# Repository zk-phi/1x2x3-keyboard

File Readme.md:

# Hifumi Keyboard

初心者向け自作キーボードキットです。

A tiny DIY keyboard for newbs.

実際にキーボードの組み立てを体験しながら自作キーボードに入門してもらえるよう、 [同人誌](https://riconken.bitbucket.io/hifumi/) の内容に合わせて設計しました。

## ファームウェア

ビルド済みのファームウェアのダウンロード (右クリックから保存してください)：

- [test キーマップ](https://raw.githubusercontent.com/zk-phi/1x2x3-keyboard/master/firmware/hifumi_test.hex)
  - 動作確認のためのキーマップです

- [default キーマップ](https://raw.githubusercontent.com/zk-phi/1x2x3-keyboard/master/firmware/hifumi_default.hex)
  - スクリーンショット (PrScr) など実用的なキーが配置されたキーマップです

ソースコードからビルドしたい場合は [QMK Firmware の公式リポジトリ](https://github.com/qmk/qmk_firmware) を参照してください。

## 組み立て

わかる人向けの近道ガイド。丁寧な解説は同人誌の方をどうぞ。

1. コンスルー (H=2.5mm) を ProMicro に実装

   https://github.com/zk-phi/keyboard-buildguide-common/blob/master/conthrough.markdown

2. SK6812mini Neopixel LED を実装 (optional)

   https://github.com/zk-phi/keyboard-buildguide-common/blob/master/neopixel.markdown

3. 1N4818 (または 1N4148w) ダイオードを実装

   https://github.com/zk-phi/keyboard-buildguide-common/blob/master/diode.markdown

4. MX 互換スイッチをトッププレートにはめ、基板と合体して半田付け

   https://github.com/zk-phi/keyboard-buildguide-common/blob/master/switch.markdown

5. M2 ネジ・高ナットでボトムプレートを連結

## 基板の発注

自分で基板を発注してみたい人向け。

1. [KiCAD](https://kicad.org/) をインストールして、プロジェクト `pcb/surfboard.pro` を開く

2. 基板データ `surfboard.kicad_pcb` をダブルクリックして基板エディタ (Pcbnew) を立ち上げる

3. `ファイル (F) > プロット (l)` で製造ファイルの出力画面を開き、設定する

   必要なレイヤーにチェックを入れる他は、基本的にデフォルトのままで問題ないと思います

   - 出力フォーマット：ガーバー

   - 含まれるレイヤー：
     - F.Cu (配線 - 表)
     - B.Cu (配線 - 裏)
     - F.SilkS (シルク印刷 - 表)
     - B.SilkS (シルク印刷 - 裏)
     - F.Mask (レジスト塗装 - 表)
     - B.Mask (レジスト塗装 - 裏)
     - Edge.Cuts (基板外形)

   - 一般オプション：
     - フットプリントの定数をプロット
     - フットプリントのリファレンスをプロット
     - 基板外形レイヤーのデータを他のレイヤーから除外 (外形専用のレイヤーに出力するので不要)
     - シルクからパッドを除外 (シルク印刷がパッドに被っているところをいい感じにしてくれる)
     - プロット前にゾーンの塗り潰しをチェック (データが変になってると警告してくれる)

   `フットプリントの xx をプロット` 系のオプションは hifumi の場合どっちでもいいです (使っていないので)。

4. `製造ファイルを出力` でガーバーデータを生成

5. `ドリルファイルを生成` でドリルファイルの出力画面を開き、設定する

   以下のデフォルト設定で特に困ったことがないです

   - ファイル形式: Excellon
   - 単位:  mm
   - ゼロのフォーマット: 小数点フォーマット
   - マップファイルフォーマット: (マップファイルは使用しません)
   - ドリルファイルオプション: 特になし
   - ドリル原点: 絶対位置

6. `ドリルファイルを生成` でドリルファイルを生成

7. 各製造業者の指定するファイル名に直す

   便利スクリプトあります: `pcb/rename-elecrow.sh`

   elecrow の場合、

   - ガーバー
     - `<プロジェクト名>-F.Cu.gbr` => `<プロジェクト名>.GTL`
     - `<プロジェクト名>-B.Cu.gbr` => `<プロジェクト名>.GBL`
     - `<プロジェクト名>-F.Mask.gbr` => `<プロジェクト名>.GTS`
     - `<プロジェクト名>-B.Mask.gbr` => `<プロジェクト名>.GBS`
     - `<プロジェクト名>-F.SilkS.gbr` => `<プロジェクト名>.GTO`
     - `<プロジェクト名>-B.SilkS.gbr` => `<プロジェクト名>.GBO`
     - `<プロジェクト名>-Edge.Cuts.gbr` => `<プロジェクト名>.GML`

   - ドリル
     - `<プロジェクト名>-PTH.drl` => `<プロジェクト名>.TXT`
     - `<プロジェクト名>-NPTH.drl` => `<プロジェクト名>-NPTH.TXT`

   と改名して、 zip に固めれば ok

   ファイルが足りない場合は手順を確認してやり直してください

8. 基板製造業者のオーダーページを開いて、ガーバーをアップロード

   サイトによっては基板サイズなどをこの時点で自動計算してくれる場合があります

9. フォームを埋めてオーダーする

   どのサイトでも確認した方がいいのは主に以下：

   - レイヤー数 layers: 2 (表と裏)
   - サイズ dimensions: 65 x 46 mm (小数点以下は切り上げで ok)
   - 作る枚数 qty
   - デザイン数 different design: 1
   - 厚み thickness: 1.6 mm
   - レジストの色 PCB (mask) color: お好みで
   - シルク印刷の色 silkscreen color: お好みで
   - パッドの表面仕上げ surface finish: HASL (Lead-free にすると鉛フリー, Gold にすると金ピカ)

   JLCPCB などの場合、追加料金を払わないと管理番号を印刷されてしまう場合があります:

   - 製造番号を消す remove order no: お好みで

   その他、サイトによって細かい技術仕様を申告する欄がありますが (すごい小さい穴を開けたい場合追加料金とか)、 hifumi の場合はそのままで大丈夫だと思います。

## プレートのレーザーカット

自分でプレートを切ってみたい人向け。

1. [OpenSCAD](https://www.openscad.org/) をインストールして、 `case/surfbord.scad` を開く

2. プログラム末尾の以下の行を書き換えて、必要な大きさのモデルを表示

   ```scad
   //cut_model_100x100();
   //cut_model_150x100();
   //cut_model_300x300();
   preview();
   ```

   デフォルトではキーボード全体のプレビューが表示されています。

   `prevew()` の行をコメントアウトして、たとえば `cut_model_100x100()` の行のコメントアウトを解除すると、 100mm x 100mm の板から切り出すためのモデルが表示されます。

   ```diff
   -//cut_model_100x100();
   +cut_model_100x100();
    //cut_model_150x100();
    //cut_model_300x300();
   -preview();
   +//preview();
   ```

   発注先のサイトや、レンタルするマシンの仕様に応じて適切なものを選んでください

   100x100 １枚からは１台分、 150x100 １枚からは２台分、 300x300 １枚からは１２台分が取れます。

3. `Design > Render (F6)` でレンダリングを実行

   一瞬で終わります

4. `File > Export > Export as DXF` で DXF ファイルを作成

   レーザーカッターでよく使われるファイル形式です

5. レーザーカットサービスに依頼したり、工房でレーザーカッターをレンタルして切る

   板は 3mm 厚のものを選んでください

   elecrow で `cut_model_100x100()` を切ってもらう場合の例:

   - Size: `10cm x 10cm Max (Thickness 3.0mm)`
   - Color: お好みで
   - Lead Time: 3-5 日固定 (執筆時点)
   - File: (`.dxf` を `.zip` に圧縮してアップロード)

   まれに変な寸法で作られてしまうことがあるので、もし連絡欄などがあれば

   - FYI: 四角い穴は 14mm x 14mm が正しいです

   などと補足をいれておいてもいいかもしれないです

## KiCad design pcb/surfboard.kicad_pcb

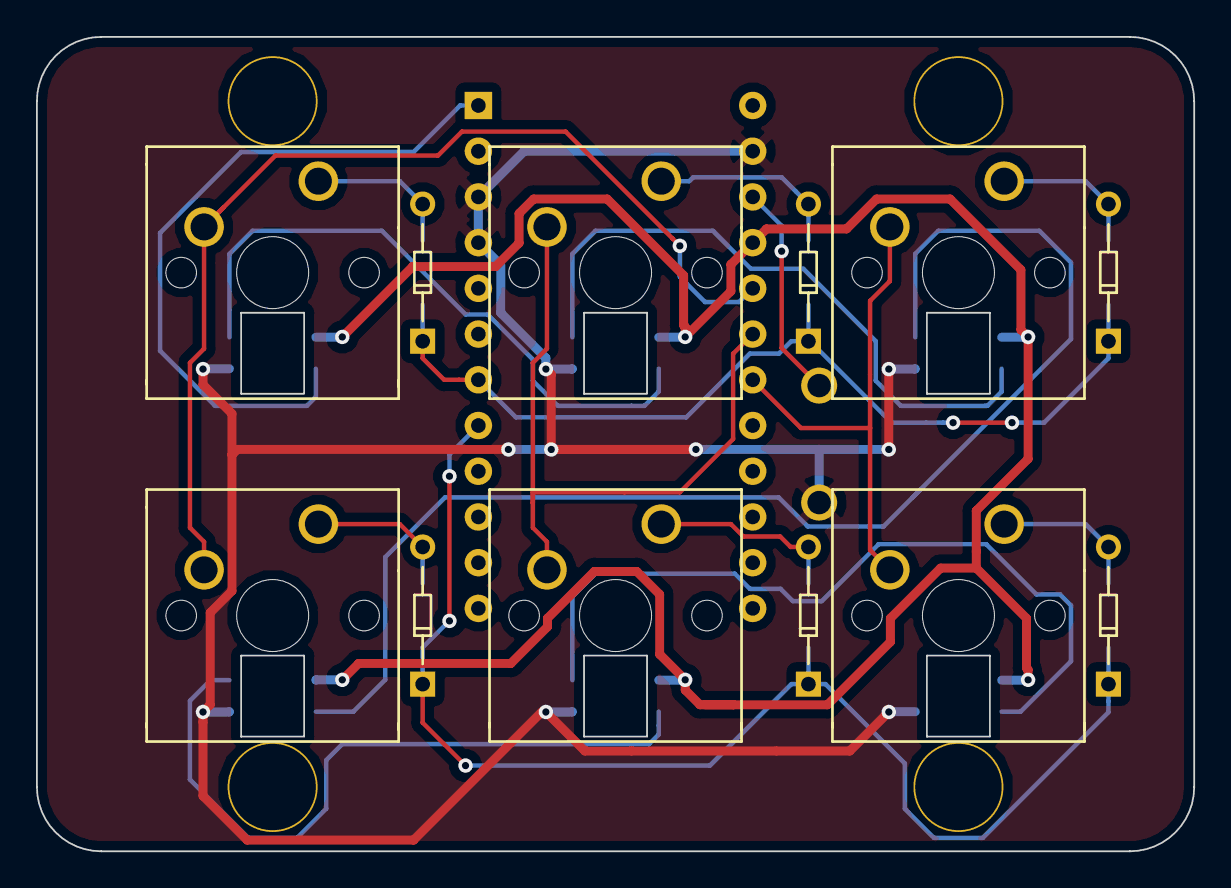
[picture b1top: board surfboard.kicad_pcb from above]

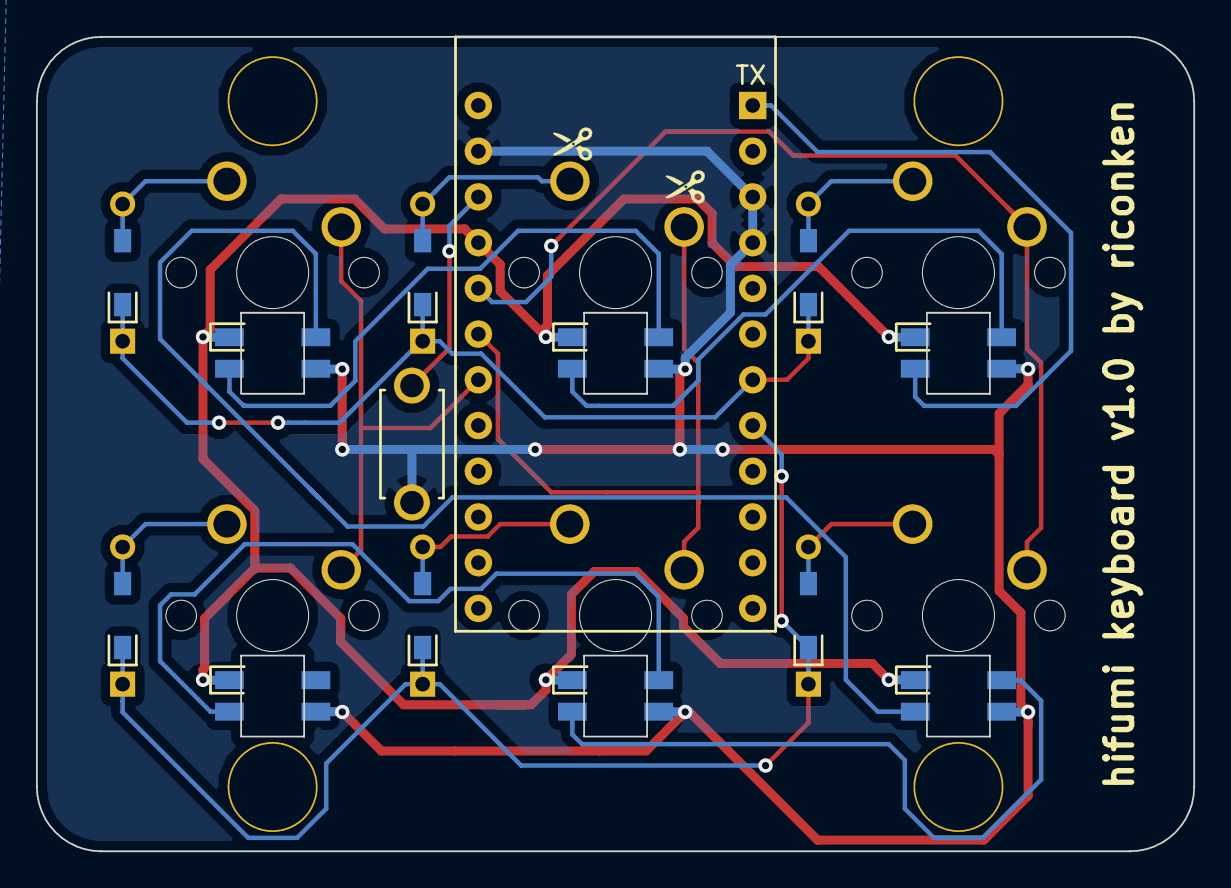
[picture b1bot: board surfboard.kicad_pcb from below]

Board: 2 copper layers, 64.3 x 45.2 mm, 24 parts (8 on the bottom side), 20 nets.

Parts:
D1, D2, D3, D4, D5, D6: D; D_TH_SMD-irreversible
L1, L2, L3, L4, L5, L6: SK6812MINI; SK6812MINI-irreversible
Ref**: Val**; HOLE
Ref**#2, Ref**#3, Ref**#4: Val**; HOLE
SW1: SW_PUSH; ResetSW-irreversible
SW2, SW3, SW4, SW5, SW6, SW7: SW_PUSH; MX_1.00u-irreversible
U1: ProMicro; ProMicro_Reversed_Conthrough-irreversible

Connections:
GND: L1.2, L2.2, L3.2, L4.2, L5.2, L6.2, SW1.2, U1.3, U1.4, U1.23
unnamed: D1.2, SW2.2
unnamed: D2.2, SW3.2
unnamed: D3.2, SW4.2
unnamed: D4.2, SW5.2
unnamed: D5.2, SW6.2
unnamed: D6.2, SW7.2
unnamed: L1.1, L3.3
unnamed: L2.1, L4.3
unnamed: L2.3, L5.1
unnamed: L3.1, L5.3
unnamed: L4.1, L6.3
VCC: L1.4, L2.4, L3.4, L4.4, L5.4, L6.4, U1.21
col0: SW2.1, SW3.1, U1.20
col1: SW4.1, SW5.1, U1.19
col2: SW6.1, SW7.1, U1.18
led: L1.3, U1.1
reset: SW1.1, U1.22
row0: D1.1, D3.1, D5.1, U1.7
row1: D2.1, D4.1, D6.1, U1.8

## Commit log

2019-01-30 Adjust LED hole positions
2019-01-31 Store ResetSW backside and move screws
2019-01-31 Add spacer models to the preview
2019-01-31 Add dimensions
2019-01-31 Fix case model
2019-01-31 Fix rename script
2019-03-04 Add 300x300 cut model for efficiency
2019-03-04 Add scissors icons and bump version
2019-03-05 Slightly move the scissor icons
2020-11-04 Add 150x100 cut model
2020-11-04 Update rename script
2020-11-04 Add readme
2020-11-04 Script benri
2021-07-18 Add pre-built firmwares
2021-07-18 Fix firmware url
2023-07-12 vial-qmk files and firmware
